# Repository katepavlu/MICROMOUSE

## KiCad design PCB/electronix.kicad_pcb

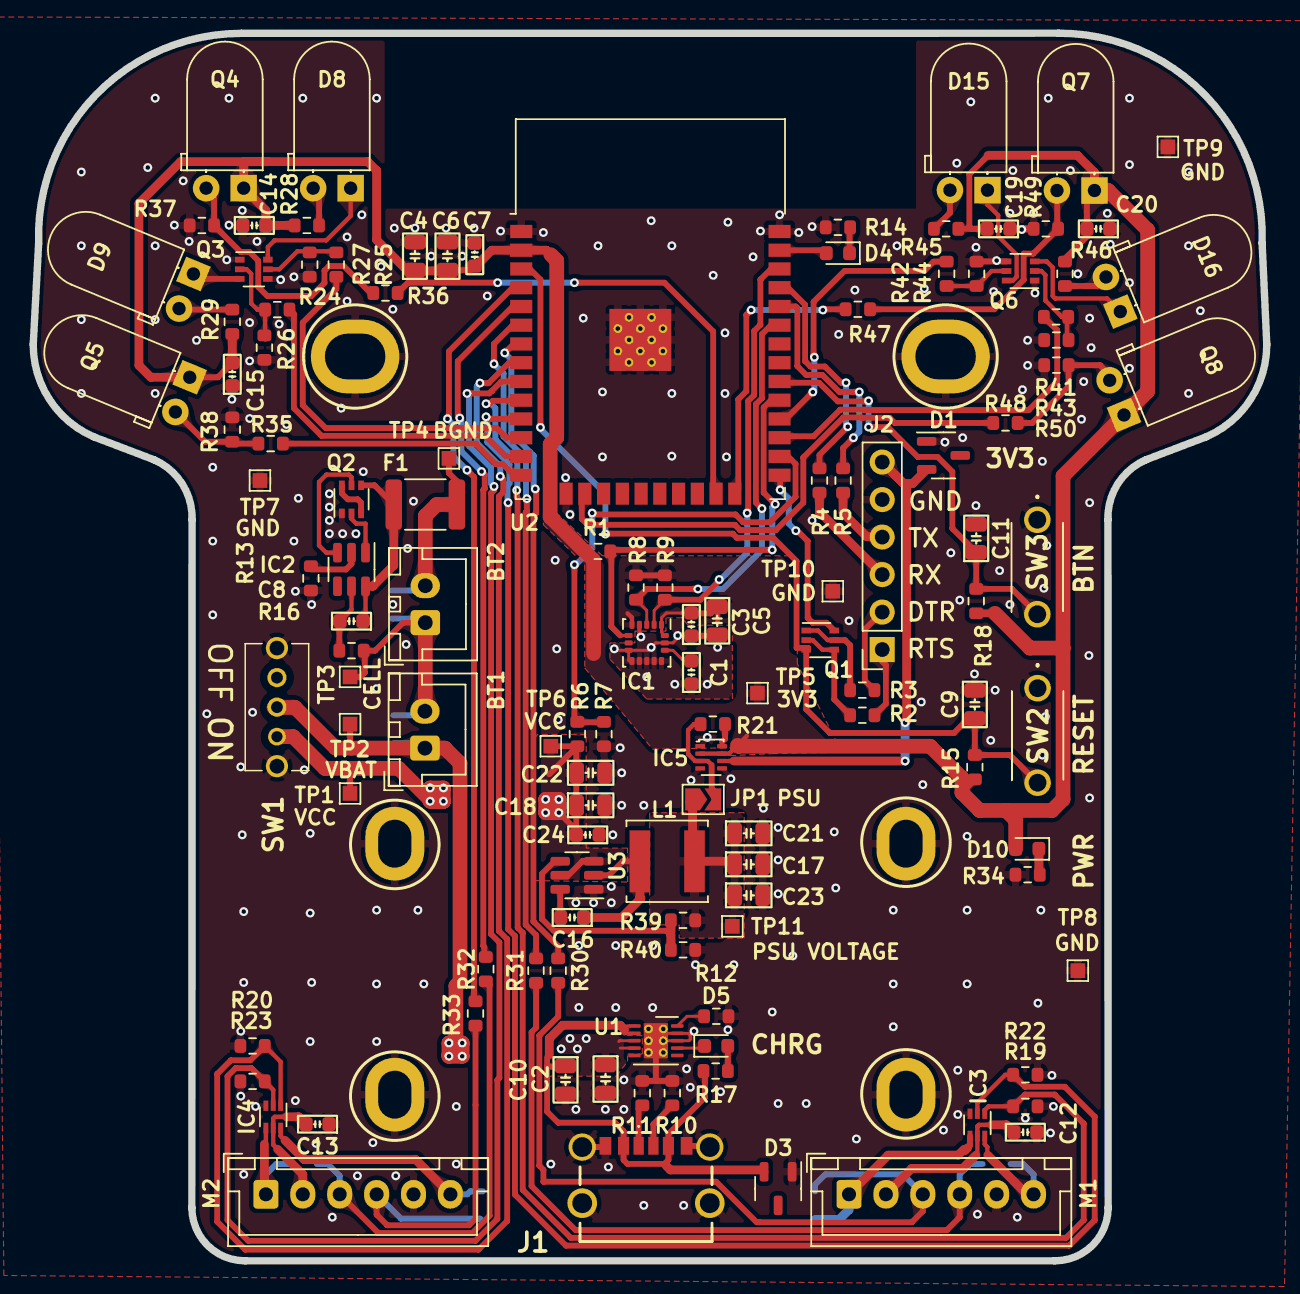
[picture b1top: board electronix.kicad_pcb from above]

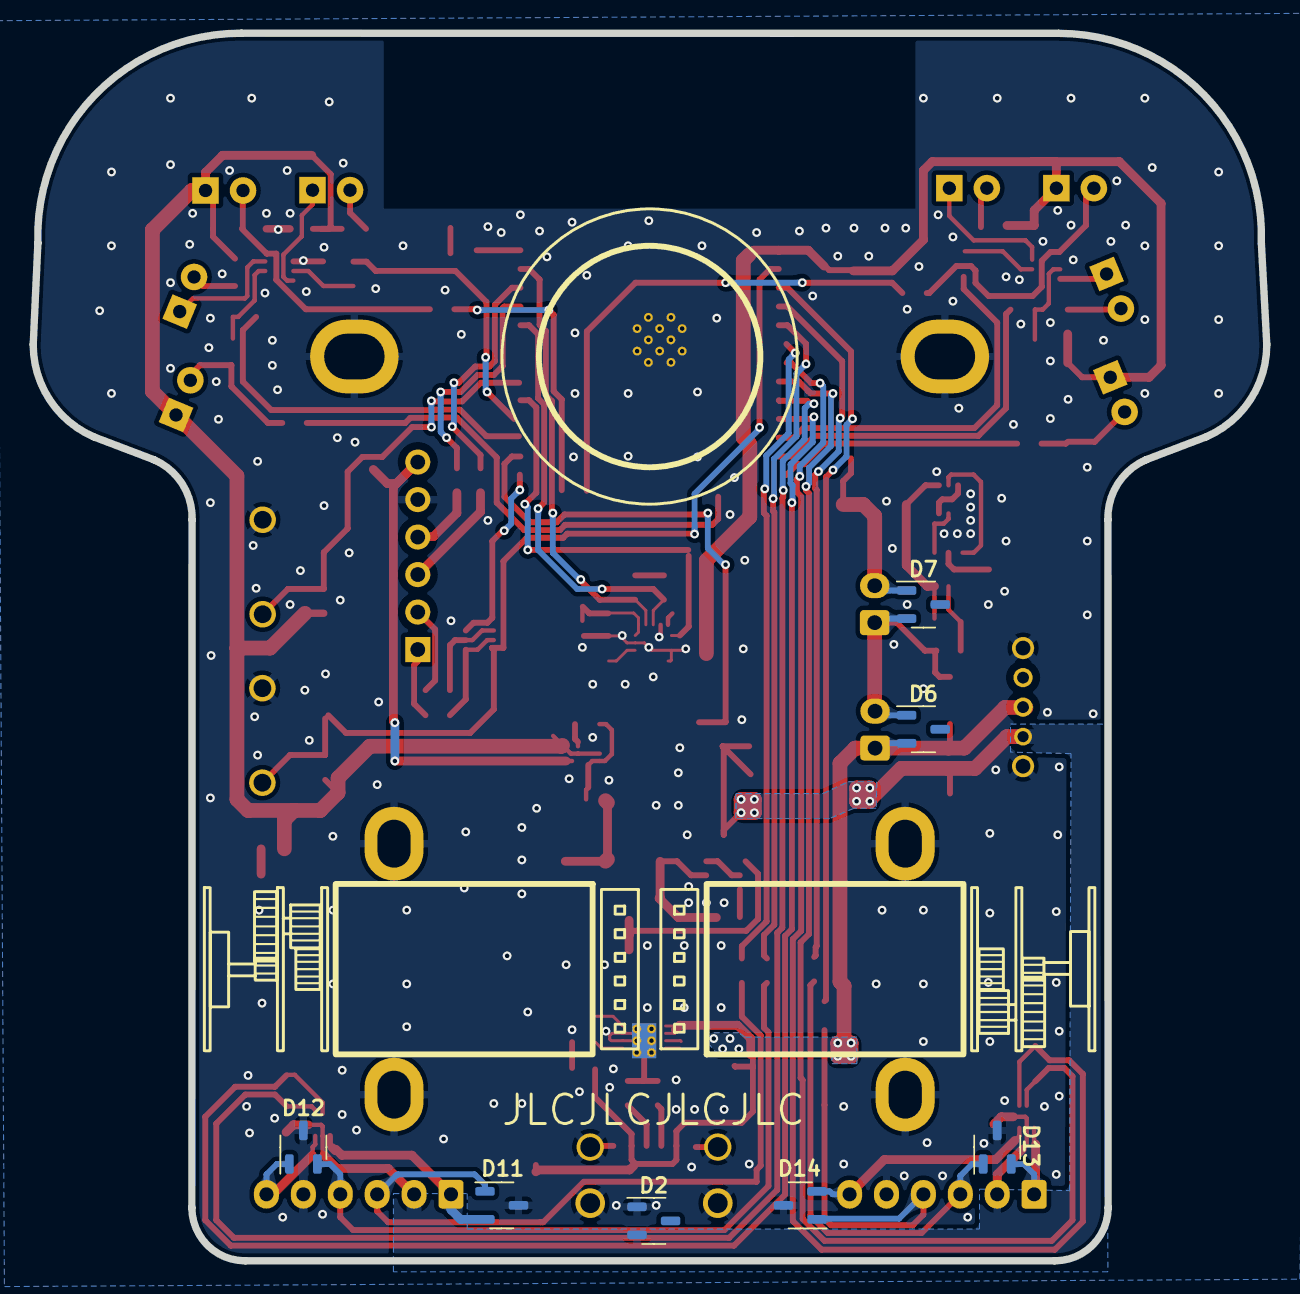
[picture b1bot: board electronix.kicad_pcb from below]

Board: 2 copper layers, 83.6 x 83.2 mm, 132 parts (10 on the bottom side), 84 nets.

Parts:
BT1, BT2: li-ion; JST_XH_B2B-XH-A_1x02_P2.50mm_Vertical
C1, C3, C7, C8, C12, C13, C14, C15, C16, C19, C20, C24: 100n; C_0603_1608Metric
C2, C4, C5, C6, C9, C10, C11, C17, C18, C21, C22, C23: 4u7/50V; C_0805_2012Metric
D1, D2, D3, D6, D7, D11, D12, D13, D14: PESD5V2S2UT; SOT-23-3
D4, D5, D10: LED; LED_0603_1608Metric
D8, D9, D15, D16: IR LED; LED_D5.0mm_Horizontal_O1.27mm_Z3.0mm
F1: Polyfuse; Fuse_1812_4532Metric
IC1: ICM-20602; LGA-16_3x3mm_P0.5mm_LayoutBorder3x5y
IC2: AP9101CK6-ANTRG1; SOT-23-6
IC3, IC4: DRV8210DRLR; SOT-563
IC5: LM66200DRLR; SOT-583-8
J1: USB-C 6pin; 1016435900011LF
J2: PRG; PinSocket_1x06_P2.54mm_Vertical
JP1: SolderJumper_2_Open; SolderJumper-2_P1.3mm_Open_TrianglePad1.0x1.5mm
L1: 3u3; L_Changjiang_FNR5040S
M1, M2: N20; JST_XH_B6B-XH-A_1x06_P2.50mm_Vertical
MNT1, MNT2: N20 encoder motor
MNT3: Ball support
Q1: UMH3N FHA; SOT-363_SC-70-6
Q2, Q3, Q6: dual NMOS; SOT-363_SC-70-6
Q4, Q5, Q7, Q8: Phototransistor; LED_D5.0mm_Horizontal_O1.27mm_Z3.0mm_IRBlack
R1, R8, R9, R15, R18, R19, R20, R21, R22, R23, R26, R27, R43, R44: 10k; R_0603_1608Metric
R2, R3, R4, R5, R24, R25, R30, R31, R32, R33, R35, R36, R41, R42, R47, R48: 100R; R_0603_1608Metric
R6, R39: 100k 1%; R_0603_1608Metric
R7, R40: 22k1 1%; R_0603_1608Metric
R10, R11: 5k1; R_0603_1608Metric
R12, R13: 2k2; R_0603_1608Metric
R14, R16, R17, R34: 330R; R_0603_1608Metric
R28, R29, R45, R46: 51R; R_0603_1608Metric
R37, R38, R49, R50: 1k8; R_0603_1608Metric
SW1: side slide; 18252321
SW2: RESET; PTS636SL50LFS
SW3: START; PTS636SL50LFS
TP1, TP2, TP3, TP4, TP5, TP6, TP7, TP8, TP9, TP10, TP11: TestPoint; TestPoint_Pad_1.0x1.0mm
U1: MCP73213-A6SI/MF; DFN-10-1EP_3x3mm_P0.5mm_EP1.65x2.38mm_ThermalVias
U2: ESP32-WROOM-32
U3: LMR51420YDDRCR; SOT-23-6

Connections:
+3V3: C3.2, C4.1, C5.1, C6.1, C7.2, C14.2, C15.2, C19.2, C20.2, D10.2 (A), IC1.1 (VDDIO), IC1.5 (CS), IC1.16 (VDD), IC5.2 (VOUT), IC5.7 (VOUT), Q4.1 (C), Q5.1 (C), Q7.1 (C), Q8.1 (C), R1.1, R8.1, R9.1, R15.1, R18.1, R28.1, R29.1, R45.1, R46.1, TP5.1, U2.2 (VDD)
+BATT: BT1.1 (+), C2.1, D6.2 (K), SW1.2, TP2.1, U1.3 (VBAT), U1.4 (VBAT)
/3V3_PRG: D1.2 (K), IC5.6 (VIN2), J2.6
/3V3_SW: IC5.3 (VIN1), JP1.2 (B), R21.1
/3V3_SW_a: C17.1, C21.1, C23.1, JP1.1 (A), L1.2, R39.1, TP11.1
/DTR: Q1.1 (E1), Q1.5 (B1), R3.1
/EN: C9.1, Q1.3 (C1), R15.2, SW2.2, U2.3 (EN)
/FB: R39.2, R40.1, U3.4 (FB)
/IMU_int: IC1.6 (INT), R1.2, U2.29 (IO5)
/IO0: Q1.6 (C1), U2.25 (IO0)
/M1c1: R31.1, U2.6 (IO34)
/M1c2: R30.1, U2.7 (IO35)
/M1in1: IC3.1 (IN1), R19.2, U2.10 (IO25)
/M1in2: IC3.2 (IN2), R22.1, U2.11 (IO26)
/M1n: D12.1 (K), IC3.6 (OUT1), M1.6
/M1p: D11.2 (K), IC3.4 (OUT2), M1.1
/M2c1: R33.1, U2.4 (SENSOR_VP)
/M2c2: R32.1, U2.5 (SENSOR_VN)
/M2in1: IC4.1 (IN1), R20.1, U2.8 (IO32)
/M2in2: IC4.2 (IN2), R23.1, U2.9 (IO33)
/M2n: D14.2 (K), IC4.6 (OUT1), M2.6
/M2p: D13.2 (K), IC4.4 (OUT2), M2.1
/RTS: Q1.2 (B1), Q1.4 (E1), R2.1
/RX: R4.1, U2.35 (TXD0/IO1)
/SCL: IC1.2 (SCL/SPC), R9.2, U2.36 (IO22)
/SDA: IC1.3 (SDA/SDI), R8.2, U2.33 (IO21)
/ST: C11.1, R18.2, SW3.2, U2.30 (IO18)
/TX: R5.1, U2.34 (RXD0/IO3)
/prox_in_fl: R24.1, U2.13 (IO14)
/prox_in_fr: R41.1, U2.27 (IO16)
/prox_in_l: R25.1, U2.12 (IO27)
/prox_in_r: R42.1, U2.28 (IO17)
/prox_out_fl: R36.1, U2.23 (IO15)
/prox_out_fr: R47.1, U2.24 (IO2)
/prox_out_l: R35.1, U2.14 (IO12)
/prox_out_r: R48.1, U2.16 (IO13)
/v_sense: R6.2, R7.1, U2.26 (IO4)
GND: C1.1, C2.2, C3.1, C4.2, C5.2, C6.2, C7.1, C9.2, C10.2, C11.2, C12.1, C13.1, C14.1, C15.1, C17.2, C18.2, C19.1, C20.1, C21.2, C22.2, C23.2, C24.1, D1.1 (K), D2.1 (K), D3.1 (K), D11.3 (A), D12.3 (A), D13.3 (A), D14.3 (A), IC1.4 (SA0/SDO), IC1.8 (FSYNC), IC1.9 (RESV_2), IC1.10 (RESV_3), IC1.11 (RESV_4), IC1.12 (RESV_5), IC1.13 (GND), IC1.15 (RESV_6), IC3.3 (GND), IC4.3 (GND), IC5.1 (GND), IC5.4 (~ON), IC5.5 (GND), J1.A12 (GND), J1.B12 (GND), J1.S1 (SHIELD), J1.S2 (SHIELD), J1.S3 (SHIELD), J1.S4 (SHIELD), J2.5, M1.5, M2.5, MNT1.M1, MNT1.M2, MNT2.M1, MNT2.M2, MNT3.M1, MNT3.M2, Q2.1 (S), Q3.1 (S), Q3.4 (S), Q6.1 (S), Q6.4 (S), R7.2, R10.2, R11.2, R12.2, R13.2, R14.1, R19.1, R20.2, R22.2, R23.2, R26.2, R27.2, R34.1, R37.1, R38.1, R40.2, R43.2, R44.2, R49.1, R50.1, SW1.MH1 (SHIELD), SW1.MH2 (SHIELD), SW2.1, SW3.1, TP7.1, TP8.1, TP9.1, TP10.1, U1.8 (VSS), U1.9 (VSS), U1.11 (EP), U2.1 (GND), U2.15 (GND), U2.38 (GND), U2.39 (GND), U3.1 (GND)
unnamed: BT1.2 (-), BT2.1 (+), D6.1 (K), D7.2 (K), R16.2, TP3.1
unnamed: BT2.2 (-), D7.1 (K), F1.2, TP4.1
unnamed: D4.2 (A), U2.37 (IO23)
unnamed: D4.1 (K), R14.2
unnamed: D5.2 (A), R17.1
unnamed: D5.1 (K), U1.7 (STAT)
unnamed: D8.2 (A), R28.2
unnamed: D8.1 (K), Q3.6 (D)
unnamed: D9.2 (A), R29.2
unnamed: D9.1 (K), Q3.3 (D)
unnamed: D10.1 (K), R34.2
unnamed: D15.2 (A), R45.2
unnamed: D15.1 (K), Q6.6 (D)
unnamed: D16.2 (A), R46.2
unnamed: D16.1 (K), Q6.3 (D)
unnamed: C1.2, IC1.14 (REGOUT)
unnamed: IC2.3 (CO), Q2.5 (G)
unnamed: IC2.1 (DO), Q2.2 (G)
unnamed: C8.2, IC2.5 (VDD), R16.1
unnamed: IC2.2 (VM), R13.1
unnamed: C8.1, F1.1, IC2.6 (VSS), Q2.4 (S)
unnamed: IC5.8 (ST), R21.2
unnamed: J1.A5 (CC1), R11.1
unnamed: J1.B5 (CC2), R10.1
unnamed: J2.1, R2.2
unnamed: J2.2, R3.2
unnamed: J2.3, R4.2
unnamed: J2.4, R5.2
unnamed: D11.1 (K), M1.3, R30.2
unnamed: D12.2 (K), M1.4, R31.2
unnamed: D13.1 (K), M2.3, R32.2
unnamed: D14.1 (K), M2.4, R33.2
unnamed: Q2.3 (D), Q2.6 (D)
unnamed: Q3.2 (G), R24.2, R26.1
unnamed: Q3.5 (G), R25.2, R27.1
unnamed: Q4.2 (E), R36.2, R37.2
unnamed: Q5.2 (E), R35.2, R38.2
unnamed: Q6.2 (G), R41.2, R43.1
unnamed: Q6.5 (G), R42.2, R44.1
unnamed: Q7.2 (E), R47.2, R49.2
unnamed: Q8.2 (E), R48.2, R50.2
unnamed: R12.1, U1.10 (PROG)
unnamed: C16.2, U3.6 (CB)
unnamed: C16.1, L1.1, U3.2 (SW)
VBUS: C10.1, D3.2 (K), J1.A9 (VBUS), J1.B9 (VBUS), R17.2, U1.1 (VDD), U1.2 (VDD)
VCC: C12.2, C13.2, C18.1, C22.1, C24.2, D2.2 (K), IC3.5 (VM), IC4.5 (VM), M1.2, M2.2, R6.1, SW1.3, TP1.1, TP6.1, U3.3 (VIN), U3.5 (EN)

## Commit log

2023-05-28 add gitignore
2023-05-29 make kicad project make motor parts start working on sensor
2023-05-31 finished schematic? removed unnecessary subfolder
2023-05-31 Add start button General schematic edits Add Mouser BOM
2023-05-31 add schematic PDF
2023-06-01 Assign fooprints Finish BOM Fix libraries Generic footprints where applicable ERC - remove erroneous net labels Start working on layout
2023-06-01 Update PDF schematic
2023-06-02 Layout Add diode on prg connector remove diode on PSU to avoid driving motors from 3V3 Footprints for motors and omniwheel
2023-06-02 add bigger ESP32 bypass
2023-06-03 Layout edits Power line hardening Fabrication outputs
2023-06-03 update output zip
2023-06-03 add outputs to gitignore
2023-06-03 new outputs
2023-06-03 deleted outputs
2023-06-03 EMI Hardening
    Rerouted back layer tracks whereever possible to create a continuous ground plane
    Added local vias to all gnd pins
    Added via stitching to overhanging areas from the front
2023-06-03 Add power source switching Add Mouser PN to parts to enable BOM generation Moved PWR indicator to side of board
2023-06-03 Finishing touches shorten ground plane cuts fillet polygon pours add test points and PSU bringup jumper differentiate capacitor footprints by silkscreen
2023-06-03 ESD hardening
2023-06-04 ESD layout edits Add TVS part numbers
2023-06-04 increase minimum hole size to 0.3
2023-08-06 Add proximity sensor simulations
2023-08-06 Start work on software - proximity sensors & state of charge
2023-08-06 extract the adc and sensors to a separate file
2023-08-06 add imu support
2023-08-07 Convert monitoring to Serial Studio
2023-08-16 Serial Studio now runs wirelessly via Bluetooth SPP Add motor co trol dependencies
